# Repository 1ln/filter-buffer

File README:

Filterbuffer pcb

Hardware Design: 

Dan Olson 
Copyright 2019

This board is currently is testing phase, use at your own risk.

This is a board designed to facilitate the filtering of high frequency line noise spikes and provide a voltage buffer to 48v power supplies. Is is meant to connect to power mosfets.

Typical uses:

Audio equipment
Industrial control systems
Pinball machines

Features:

Two large capacitor units.
48v power led.
In-rush current limitor.
250v safety fuse.
Two independent non-filtered sections for powering 12v and 5v systems.

TODO:

Add bleedoff resistor or circuit.

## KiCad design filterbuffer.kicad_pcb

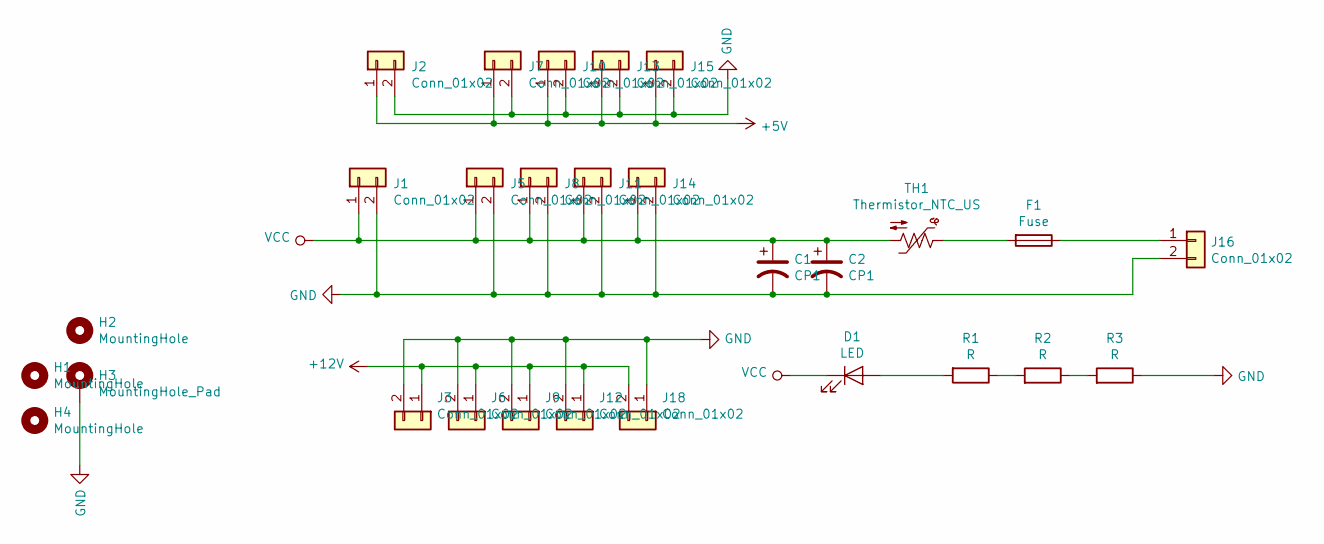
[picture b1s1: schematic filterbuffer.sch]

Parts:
C1, C2: CP1; CP_Radial_D35.0mm_P10.00mm_SnapIn
D1: LED; LED_1206_3216Metric
F1: Fuse; FUSE_696105003002
H1, H2, H4: MountingHole; MountingHole_3.2mm_M3
H3: MountingHole_Pad; MountingHole_3.2mm_M3_Pad_Via
J1, J5, J8, J11, J14, J16: Conn_01x02; TerminalBlock_Phoenix_PT-1,5-2-3.5-H_1x02_P3.50mm_Horizontal
J2, J3, J6, J7, J9, J10, J12, J13, J15, J18: Conn_01x02; PinHeader_1x02_P2.54mm_Vertical
R1, R2, R3: R; R_1206_3216Metric_Pad1.42x1.75mm_HandSolder
TH1: Thermistor_NTC_US; R_Radial_Power_L16.1mm_W9.0mm_P7.37mm

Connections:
+5V: J2.1, J7.1, J10.1, J13.1, J15.1
+12V: J3.1, J6.1, J9.1, J12.1, J18.2
GND: C1.2, C2.2, H3.1, J1.2, J2.2, J3.2, J5.2, J6.2, J7.2, J8.2, J9.2, J10.2, J11.2, J12.2, J13.2, J14.2, J15.2, J16.2, J18.1, R3.1
unnamed: D1.2 (A), R1.2
unnamed: F1.1, J16.1
unnamed: F1.2, TH1.1
unnamed: R1.1, R2.2
unnamed: R2.1, R3.2
VCC: C1.1, C2.1, D1.1 (K), J1.1, J5.1, J8.1, J11.1, J14.1, TH1.2

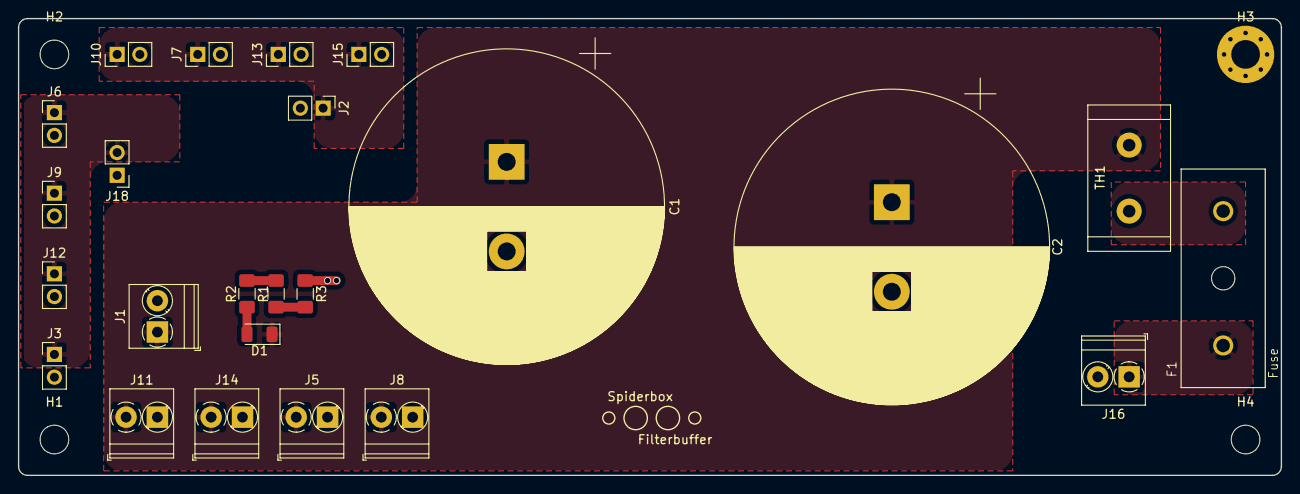
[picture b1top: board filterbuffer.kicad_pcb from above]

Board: 2 copper layers, 141.0 x 51.0 mm, 28 parts (0 on the bottom side), 9 nets.

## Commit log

2019-04-12 add 3d image
2019-04-13 add system ground
2019-04-13 add gerber
2019-04-14 layout redesign
2019-04-14 update gerber
2019-05-08 update layout
2019-05-13 update png
2019-05-13 add readme
